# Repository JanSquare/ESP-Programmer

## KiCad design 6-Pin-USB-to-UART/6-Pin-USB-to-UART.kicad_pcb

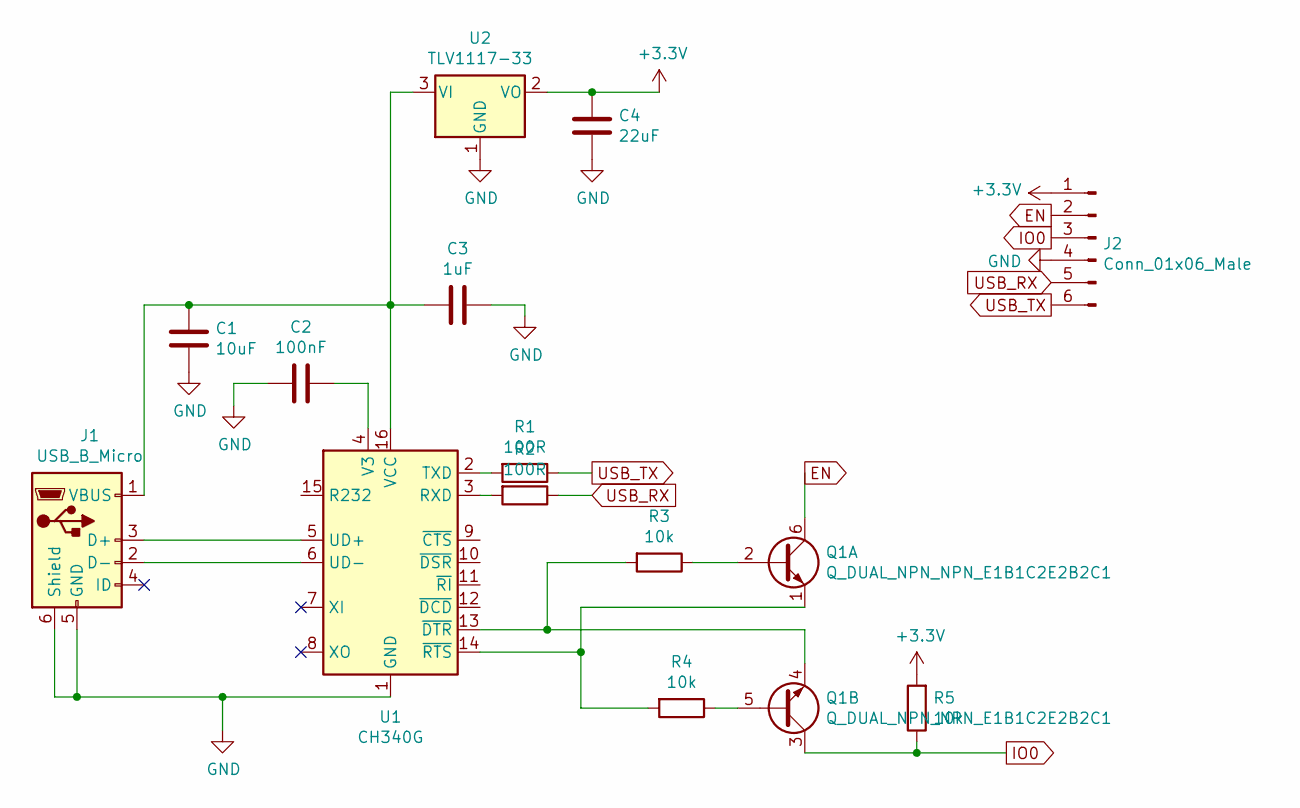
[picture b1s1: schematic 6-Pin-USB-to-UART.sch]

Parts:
C1: 10uF; C_0805_2012Metric
C2: 100nF; C_0603_1608Metric
C3: 1uF; C_0603_1608Metric
C4: 22uF; C_0805_2012Metric
J1: USB_B_Micro; USB_Micro-B_Molex-105017-0001
J2: Conn_01x06_Male; PinHeader_1x06_P2.54mm_Vertical
Q1: Q_DUAL_NPN_NPN_E1B1C2E2B2C1; SOT-363_SC-70-6
R1, R2: 100R; R_0603_1608Metric
R3, R4, R5: 10k; R_0603_1608Metric
U1: CH340G; SOIC-16_3.9x9.9mm_P1.27mm
U2: TLV1117-33; SOT-223-3_TabPin2

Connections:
+3V3: C4.2, J2.1, R5.2, U2.2 (VO)
EN: J2.2, Q1.6 (C1)
GND: C1.1, C2.2, C3.1, C4.1, J1.5 (GND), J1.6 (Shield), J2.4, U1.1 (GND), U2.1 (GND)
IO0: J2.3, Q1.3 (C2), R5.1
unnamed: C1.2, C3.2, J1.1 (VBUS), U1.16 (VCC), U2.3 (VI)
unnamed: C2.1, U1.4 (V3)
unnamed: J1.2 (D-), U1.6 (UD-)
unnamed: J1.3 (D+), U1.5 (UD+)
unnamed: Q1.1 (E1), R4.2, U1.14 (~RTS)
unnamed: Q1.2 (B1), R3.1
unnamed: Q1.4 (E2), R3.2, U1.13 (~DTR)
unnamed: Q1.5 (B2), R4.1
unnamed: R1.2, U1.2 (TXD)
unnamed: R2.2, U1.3 (RXD)
USB_RX: J2.5, R2.1
USB_TX: J2.6, R1.1

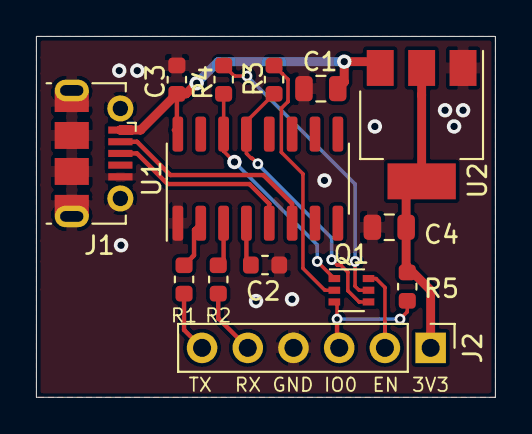
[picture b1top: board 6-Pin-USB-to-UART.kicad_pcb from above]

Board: 2 copper layers, 25.5 x 20.1 mm, 14 parts (0 on the bottom side), 16 nets.
